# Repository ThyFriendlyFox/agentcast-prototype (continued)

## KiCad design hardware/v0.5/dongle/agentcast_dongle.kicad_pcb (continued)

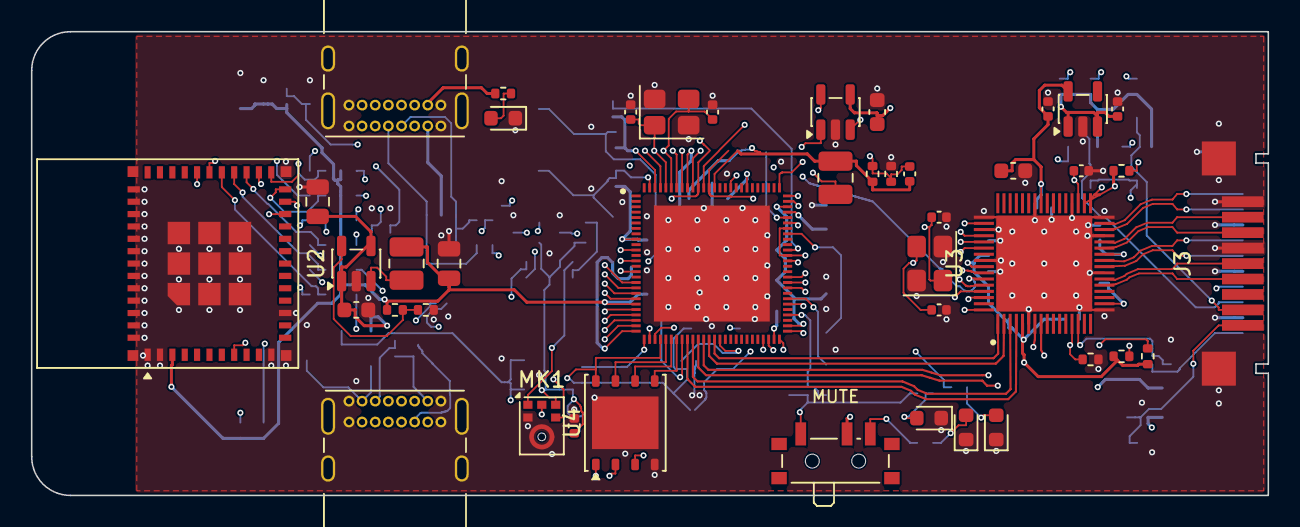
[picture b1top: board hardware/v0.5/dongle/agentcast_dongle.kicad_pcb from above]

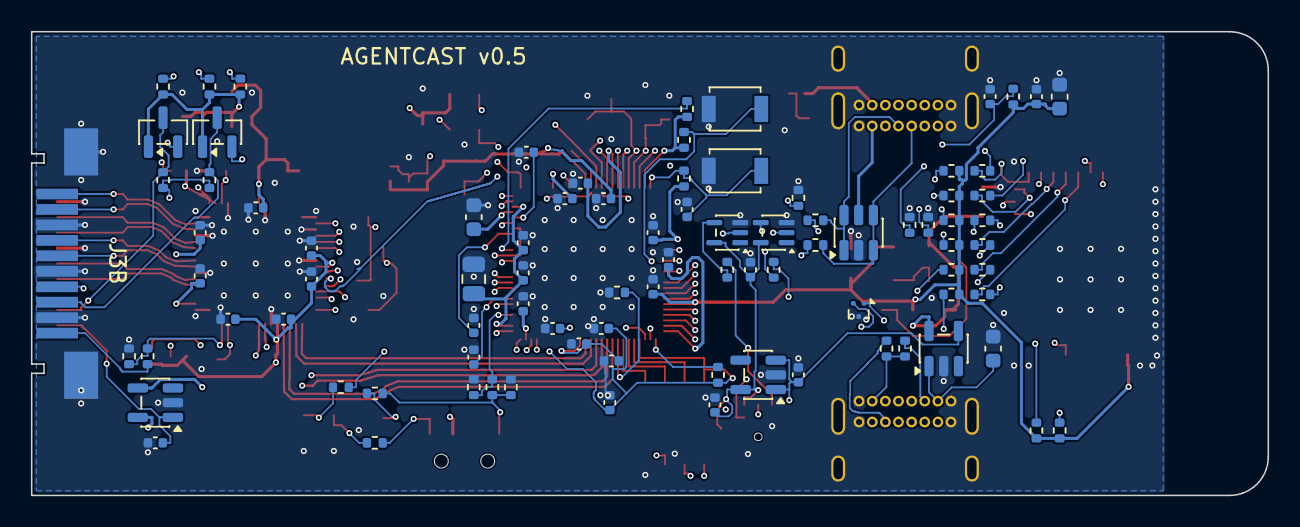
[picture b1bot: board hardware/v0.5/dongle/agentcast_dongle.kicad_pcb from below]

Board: 8 copper layers, 80.0 x 30.0 mm, 132 parts (89 on the bottom side), 100 nets.

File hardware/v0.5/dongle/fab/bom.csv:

"Refs","Value","Footprint","Qty","DNP"
"C1","100n","Capacitor_SMD:C_0402_1005Metric","1",""
"C2","100n","Capacitor_SMD:C_0402_1005Metric","1",""
"C3","100n","Capacitor_SMD:C_0402_1005Metric","1",""
"C4","100n","Capacitor_SMD:C_0402_1005Metric","1",""
"C5","100n","Capacitor_SMD:C_0402_1005Metric","1",""
"C6","100n","Capacitor_SMD:C_0402_1005Metric","1",""
"C7","100n","Capacitor_SMD:C_0402_1005Metric","1",""
"C8","100n","Capacitor_SMD:C_0402_1005Metric","1",""
"C9","100n","Capacitor_SMD:C_0402_1005Metric","1",""
"C10","100n","Capacitor_SMD:C_0402_1005Metric","1",""
"C11","100n","Capacitor_SMD:C_0402_1005Metric","1",""
"C12","100n","Capacitor_SMD:C_0402_1005Metric","1",""
"C13","10u","Capacitor_SMD:C_0603_1608Metric","1",""
"C14","22u","Capacitor_SMD:C_0805_2012Metric","1",""
"C15","1u","Capacitor_SMD:C_0402_1005Metric","1",""
"C16","1u","Capacitor_SMD:C_0402_1005Metric","1",""
"C17","1u","Capacitor_SMD:C_0402_1005Metric","1",""
"C18","1u","Capacitor_SMD:C_0402_1005Metric","1",""
"C19","4.7u","Capacitor_SMD:C_0603_1608Metric","1",""
"C20","22p","Capacitor_SMD:C_0402_1005Metric","1",""
"C21","12p","Capacitor_SMD:C_0402_1005Metric","1",""
"C22","12p","Capacitor_SMD:C_0402_1005Metric","1",""
"C23","1u","Capacitor_SMD:C_0402_1005Metric","1",""
"C24","100n","Capacitor_SMD:C_0402_1005Metric","1",""
"C25","100n","Capacitor_SMD:C_0402_1005Metric","1",""
"C26","100n","Capacitor_SMD:C_0402_1005Metric","1",""
"C27","100n","Capacitor_SMD:C_0402_1005Metric","1",""
"C28","100n","Capacitor_SMD:C_0402_1005Metric","1",""
"C29","100n","Capacitor_SMD:C_0402_1005Metric","1",""
"C30","100n","Capacitor_SMD:C_0402_1005Metric","1",""
"C31","100n","Capacitor_SMD:C_0402_1005Metric","1",""
"C32","10u","Capacitor_SMD:C_0603_1608Metric","1",""
"C33","2.2n","Capacitor_SMD:C_0402_1005Metric","1",""
"C34","12p","Capacitor_SMD:C_0402_1005Metric","1",""
"C35","12p","Capacitor_SMD:C_0402_1005Metric","1",""
"C36","1u","Capacitor_SMD:C_0402_1005Metric","1",""
"C37","1u","Capacitor_SMD:C_0402_1005Metric","1",""
"C38","100n","Capacitor_SMD:C_0402_1005Metric","1",""
"C39","10u","Capacitor_SMD:C_0603_1608Metric","1",""
"C40","100n","Capacitor_SMD:C_0402_1005Metric","1",""
"C41","1u","Capacitor_SMD:C_0402_1005Metric","1",""
"C42","10u","Capacitor_SMD:C_0603_1608Metric","1",""
"C43","22u","Capacitor_SMD:C_0805_2012Metric","1",""
"C44","22u","Capacitor_SMD:C_0805_2012Metric","1",""
"C45","10u","Capacitor_SMD:C_0603_1608Metric","1",""
"C46","1u","Capacitor_SMD:C_0402_1005Metric","1",""
"C47","1u","Capacitor_SMD:C_0402_1005Metric","1",""
"C48","100n","Capacitor_SMD:C_0402_1005Metric","1",""
"C49","100n","Capacitor_SMD:C_0402_1005Metric","1",""
"D1","green LIVE","LED_SMD:LED_0603_1608Metric","1",""
"D2","red MUTED","LED_SMD:LED_0603_1608Metric","1",""
"D3","green PWR","LED_SMD:LED_0603_1608Metric","1",""
"D4","amber STATE","LED_SMD:LED_0603_1608Metric","1",""
"J3","HDMI-003","Agentcast:HDMI_A_Plug_XUNPU_HDMI-003_Top","1",""
"J4","USB4085-GF-A","Connector_USB:USB_C_Receptacle_GCT_USB4085","1",""
"J6","USB4085-GF-A","Connector_USB:USB_C_Receptacle_GCT_USB4085","1",""
"L1","2.2u","Inductor_SMD:L_1008_2520Metric","1",""
"L2","2.2u","Inductor_SMD:L_1008_2520Metric","1",""
"MK1","ICS-43434","Sensor_Audio:InvenSense_ICS-43434-6_3.5x2.65mm","1",""
"Q1","BSS138","Package_TO_SOT_SMD:SOT-23","1",""
"Q2","BSS138","Package_TO_SOT_SMD:SOT-23","1",""
"R1","4.02k","Resistor_SMD:R_0402_1005Metric","1",""
"R2","499k","Resistor_SMD:R_0402_1005Metric","1",""
"R3","499k","Resistor_SMD:R_0402_1005Metric","1",""
"R4","10k","Resistor_SMD:R_0402_1005Metric","1",""
"R5","10k","Resistor_SMD:R_0402_1005Metric","1",""
"R6","10k","Resistor_SMD:R_0402_1005Metric","1",""
"R7","10k","Resistor_SMD:R_0402_1005Metric","1",""
"R8","6.04k","Resistor_SMD:R_0402_1005Metric","1",""
"R9","10k","Resistor_SMD:R_0402_1005Metric","1",""
"R10","4.7k","Resistor_SMD:R_0402_1005Metric","1",""
"R11","4.7k","Resistor_SMD:R_0402_1005Metric","1",""
"R12","18k","Resistor_SMD:R_0402_1005Metric","1",""
"R13","10k","Resistor_SMD:R_0402_1005Metric","1",""
"R14","1.8k","Resistor_SMD:R_0402_1005Metric","1",""
"R15","4.7k","Resistor_SMD:R_0402_1005Metric","1",""
"R16","1.8k","Resistor_SMD:R_0402_1005Metric","1",""
"R17","4.7k","Resistor_SMD:R_0402_1005Metric","1",""
"R18","27k","Resistor_SMD:R_0402_1005Metric","1",""
"R19","10k","Resistor_SMD:R_0402_1005Metric","1",""
"R20","10k","Resistor_SMD:R_0402_1005Metric","1",""
"R21","10k","Resistor_SMD:R_0402_1005Metric","1",""
"R22","22","Resistor_SMD:R_0402_1005Metric","1",""
"R23","10k","Resistor_SMD:R_0402_1005Metric","1",""
"R24","22","Resistor_SMD:R_0402_1005Metric","1",""
"R25","10k","Resistor_SMD:R_0402_1005Metric","1",""
"R26","22","Resistor_SMD:R_0402_1005Metric","1",""
"R27","10k","Resistor_SMD:R_0402_1005Metric","1",""
"R28","22","Resistor_SMD:R_0402_1005Metric","1",""
"R29","10k","Resistor_SMD:R_0402_1005Metric","1",""
"R30","22","Resistor_SMD:R_0402_1005Metric","1",""
"R31","10k","Resistor_SMD:R_0402_1005Metric","1",""
"R32","22","Resistor_SMD:R_0402_1005Metric","1",""
"R33","10k","Resistor_SMD:R_0402_1005Metric","1",""
"R34","5.1k","Resistor_SMD:R_0402_1005Metric","1",""
"R35","5.1k","Resistor_SMD:R_0402_1005Metric","1",""
"R36","22","Resistor_SMD:R_0402_1005Metric","1",""
"R37","22","Resistor_SMD:R_0402_1005Metric","1",""
"R38","100k","Resistor_SMD:R_0402_1005Metric","1",""
"R39","22.1k","Resistor_SMD:R_0402_1005Metric","1",""
"R40","56k","Resistor_SMD:R_0402_1005Metric","1",""
"R41","56k","Resistor_SMD:R_0402_1005Metric","1",""
"R42","100k","Resistor_SMD:R_0402_1005Metric","1",""
"R43","1k","Resistor_SMD:R_0402_1005Metric","1",""
"R44","1k","Resistor_SMD:R_0402_1005Metric","1",""
"R45","10k","Resistor_SMD:R_0402_1005Metric","1",""
"R46","100k","Resistor_SMD:R_0402_1005Metric","1",""
"R47","33","Resistor_SMD:R_0402_1005Metric","1",""
"R48","33","Resistor_SMD:R_0402_1005Metric","1",""
"R49","100k","Resistor_SMD:R_0402_1005Metric","1",""
"R50","2.2k","Resistor_SMD:R_0402_1005Metric","1",""
"R51","330","Resistor_SMD:R_0402_1005Metric","1",""
"SW1","BOOT","Button_Switch_SMD:SW_SPST_B3U-1000P","1",""
"SW2","PCM12SMTR","Button_Switch_SMD:SW_SPDT_PCM12","1",""
"SW3","RESET","Button_Switch_SMD:SW_SPST_B3U-1000P","1",""
"U1","ESP32-P4NRW32","Agentcast:QFN-104-1EP_10x10mm_P0.35mm_EP7.5x7.5mm","1",""
"U2","ESP32-C6-MINI-1","RF_Module:ESP32-C6-MINI-1","1",""
"U3","LT8912B","Agentcast:QFN-64-1EP_7.5x7.5mm_P0.4mm_EP6.2x6.2mm","1",""
"U4","W25Q128JVPIQ","Package_SON:WSON-8-1EP_6x5mm_P1.27mm_EP3.4x4.3mm","1",""
"U5","TLV62569DBV","Package_TO_SOT_SMD:SOT-23-5","1",""
"U6","TLV75518PDBV","Package_TO_SOT_SMD:SOT-23-5","1",""
"U7","TPS2051CDBV","Package_TO_SOT_SMD:SOT-23-5","1",""
"U8","USBLC6-2SC6","Package_TO_SOT_SMD:SOT-23-6","1",""
"U9","TLV62569DBV","Package_TO_SOT_SMD:SOT-23-5","1",""
"U10","TPD2EUSB30","Package_TO_SOT_SMD:Texas_DRT-3","1",""
"U11","TPS2051CDBV","Package_TO_SOT_SMD:SOT-23-5","1",""
"U12","AP2112K-1.8","Package_TO_SOT_SMD:SOT-23-5","1",""
"U13","74LVC1G34","Package_TO_SOT_SMD:SOT-353_SC-70-5","1",""
"U14","74LVC1G34","Package_TO_SOT_SMD:SOT-353_SC-70-5","1",""
"Y1","40MHz 10ppm","Crystal:Crystal_SMD_3225-4Pin_3.2x2.5mm","1",""
"Y2","25MHz (confirm)","Crystal:Crystal_SMD_3225-4Pin_3.2x2.5mm","1",""

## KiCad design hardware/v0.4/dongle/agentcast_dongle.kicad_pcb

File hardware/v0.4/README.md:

# Agentcast dongle v0.4

> **Archived** at commit `223e73b`. Superseded by [v0.5](../v0.5/) (own computer, 68 x 26 mm).
> Made from [v0.3](../v0.3/) (commit `f83c855`). v0.4 replaces the
> HDMI receptacle with a male HDMI Type-A plug: the stick goes straight into the TV.

One board, 67 x 46 mm, 4 layers. A Raspberry Pi Compute Module 5 sits on top.
A male HDMI plug clamps the near end of the board, like a Roku or Fire TV stick.

| | v0.3 | v0.4 |
|---|---|---|
| HDMI | Amphenol 10029449 receptacle; needed a male-to-male adapter | Male Type-A plug on the board edge (XUNPU HDMI-003 class); plugs into the TV |
| HDMI pairs | all four on F.Cu | D2 and D0 on F.Cu to the top contacts; D1 and CK drop through a via pair to the bottom contacts |
| Size, ports, mic, mute | as v0.3 | unchanged |

**Do not order yet.** The plug's footprint follows the HDMI Type-A contact
layout, but four of its numbers are the part's own and need its drawing (see
"HDMI plug").

| From above | From below | With the CM5 |
|---|---|---|
|  |  |  |
|  |  |  |

Schematic: [`dongle/docs/schematic.png`](dongle/docs/schematic.png).
Commands: `workcenter render dongle --views all --spin-frames 36 --strict`; the view
from below adds `--views spin --spin-frames 36 --spin-tilt -125`; the assembly
pictures come from `make assembly`.

## HDMI plug

A board-edge HDMI plug has its contacts in two rows that clamp the board: one
row solders to pads on the top face, the other to pads on the bottom face, both
at the board's edge. KiCad's library has no such footprint, so
[`library/gen_library.py`](library/gen_library.py) draws one as two footprints:
`HDMI_A_Plug_Edge_Top` (J3) and `HDMI_A_Plug_Edge_Bottom` (J3B, on B.Cu, not in
the BOM).

| Number | Value | Source |
|---|---|---|
| Contacts | 19, odd and even pins in two rows | HDMI Type-A pinout |
| Pitch in a row | 1.0 mm, the rows 0.5 mm apart | HDMI Type-A pinout |
| Shell | 13.9 x 4.45 mm, 11.5 mm beyond the edge (3D box) | HDMI Type-A plug size; length estimated |
| Pad size | 0.6 x 2.0 mm, ending 0.3 mm from the edge | **to confirm** on the part's drawing |
| Clamp tabs | 1.2 x 2.4 mm, 6.6 mm each side of the axis, both faces | **to confirm** |
| Odd row on the top face | yes (`ODD_ON_TOP`) | **to confirm** |
| Board thickness it clamps | 1.6 mm (this board) | **to confirm**; many stick plugs clamp 1.0 or 1.2 mm |

The candidate part is XUNPU HDMI-003 (LCSC
[C5723179](https://www.lcsc.com/product-detail/C5723179.html)), listed as a
19-pin male HDMI-A plug, "clamp plate" mount. Its drawing is a PDF I could not
open from this session. With the drawing, each **to confirm** line above is one
constant in `gen_library.py` (and `thickness=` on the design if the board must
be thinner); `make design` then regenerates the board.

If the odd row turns out to be on the bottom face, D2 and D0 move to the bottom
and D1 and CK to the top: `route_tmds()` reads the pads, so the pairs follow.

## Why it is not narrower

The CM5 is 55 x 40 mm, so a stick built on it is at least 40 mm wide. v0.4 is
46 mm: 40 for the module and a 6 mm strip below it that carries the four HDMI
pairs, the mic, two LEDs and the mute switch. A Roku Streaming Stick is about
20 mm wide; that size needs a smaller computer than the CM5.

## CM5 position, checked

Raspberry Pi's CM5 3D model (RP-007222-DD-2, "rpi-cm5 3D_STEP", from
[rpltd.co/cm5-design-files](https://rpltd.co/cm5-design-files)) gives, in the
module's frame (antenna edge at x = 0, y up):

| Feature | 3D model | This board |
|---|---|---|
| Board-to-board connectors (Amphenol 10164228-1001A1RLF) | centres (25.0, 3.0) and (25.0, 37.0) mm | J1, J2 at 25.0 mm from the antenna edge, 3.0 mm in from each long edge |
| M2.5 holes | (3.5, 3.5), (51.5, 3.5), (3.5, 36.5), (51.5, 36.5) mm, 2.7 mm | H1-H4 at the same points |
| U.FL | (2.567, 31.0) mm | matches datasheet Figure 4 (2.567 mm from the antenna edge, 9 mm from the top) |

The 3D model's connector names (P1, P2) do not follow the pin numbers, so which
socket carries pins 1-100 still comes from Figure 4's labels: the one nearer the
U.FL. The assembly pictures put Raspberry Pi's model on the board with these
numbers; its U.FL lands on the J1 side, as Figure 4 shows.

## Fabrication files

[`dongle/fab/`](dongle/fab/), made by `make fab`: Gerbers with the drill file
and job file (`gerbers/`), the BOM (`bom.csv`), the schematic PDF, and a
pick-and-place file for both faces (`agentcast_dongle-pos.csv`, KiCad CSV, mm,
page coordinates: the board's top-left corner is at (100, -100)). The BOM lists
values and footprints; part numbers for the passives are not chosen yet.

## Gate results

`workcenter gates dongle`:

| Gate | Result |
|---|---|
| ERC | PASS, 0 errors, 0 warnings |
| DRC | PASS, 0 errors, 0 unconnected, 0 parity; 4 silk warnings where the USB-C bodies and the mute switch cross the edge, as designed |
| SIM | PASS, 1 deck (`mic_live`) |
| EXPORT | PASS, 24 Gerber files, drill, BOM, PDF |

`workcenter render dongle --strict` passes: every part has a 3D body.

## Layout

| Where | What |
|---|---|
| Far end (x = 0) | The CM5's antenna. No copper and no parts under it, on any layer. |
| Under the module, F.Cu | J1, J2 and the HDMI pairs' risers. Nothing else: the module sits 1.5 mm above. |
| Strip below the module, F.Cu | Mic MK1 (sound hole at x 2.8, y 44.21 mm), LIVE and MUTED LEDs, mute switch SW2 (out of the long side), and the four HDMI pairs in lanes. |
| Near end | The male HDMI plug clamps the edge (J3 top contacts, J3B bottom contacts). USB-C power J4 out of the top side, USB-C external mic J6 out of the bottom side. |
| B.Cu | The plug's bottom contacts, and 32 small parts: power switches, ESD, clock buffers, PWR / ACT / STATE LEDs, resistors, capacitors, the BOOT button. |

## How it maps to the spec

| Spec requirement | v0.4 answer |
|---|---|
| HDMI dongle, the TV shows only what the dongle sends | CM5 HDMI0 to a male HDMI plug (J3, J3B) on the stick's end: it plugs into the TV. |
| A separate power supply | USB-C (J4). The CM5 negotiates 5 V up to 5 A itself (CM5 datasheet 2.12.1). |
| Hear the room; tell speakers apart | On-board ICS-43434 mic. Speakers are told apart by voice in the cloud, so one mic is enough. |
| A better mic when the room needs it | USB-C host port (J6) for a USB mic. |
| A physical mute; the indicator tied to mic power | SW2 cuts MIC_VDD. The green LIVE LED runs from MIC_VDD; the red MUTED LED from the switch's other throw. |
| Software cannot turn a mic on in secret | MIC_VDD powers the on-board mic, its clock buffers, and U3's enable, which powers J6. No GPIO can do either. |
| TV control over HDMI-CEC | HDMI pin 13 to the CM5's HDMI0_CEC. |
| Recovery without IT | BOOT button (nRPIBOOT) and USB data on J4 for `rpiboot`. |

## Part choices

| Ref | Part | Why |
|---|---|---|
| J1, J2 | Hirose DF40C-100DS-0.4V | The CM5 sockets. 1.5 mm stack height (CM5 datasheet 4.1.1). |
| J3, J3B | HDMI Type-A male plug, board-edge clamp (XUNPU HDMI-003 class) | Plugs straight into the TV. One part, two footprints (top and bottom contacts). See "HDMI plug". |
| J4, J6 | GCT USB4085 | USB-C 2.0, through-hole pins: strong against a plug pulled sideways, and KiCad has its 3D body. J4: power and flashing. J6: host port with 56 k Rp on each CC. |
| U1, U4 | ST USBLC6-2SC6 | ESD on each USB 2.0 pair. |
| U2 | TI TPS2051CDBV | HDMI +5V: current limit and reverse-current blocking. EN from +3V3. |
| U3 | TI TPS2051CDBV | External mic power. EN from MIC_VDD, so mute cuts it. |
| MK1 | TDK InvenSense ICS-43434 | I2S mic, 24-bit, bottom port. |
| U5, U6 | 74LVC1G34 | BCLK and WS buffers on MIC_VDD (Ioff): a muted mic gets no power through its clock pins. |
| SW2 | C&K PCM12SMTR | Mute slide switch, out of the long side. |
| SW1 | Omron B3U-1000P | BOOT button, bottom face. |

## Pin plan (CM5)

Read from the CM5 datasheet: the GPIO alternate-function table (section 2.9)
and the pinout (section 4.2). GPIO_VREF (pin 78) is tied to CM5_3.3V.

| Signal | CM5 pin | GPIO | Function | Goes to |
|---|---|---|---|---|
| I2S_BCLK | 49 | GPIO18 | I2S0_SCLK (alt a2), master | U5, R1, MK1 |
| I2S_WS | 26 | GPIO19 | I2S0_WS (alt a2) | U6, R2, MK1 |
| MIC_SD0 | 27 | GPIO20 | I2S0_SDI[0] (alt a2) | MK1 (left channel) |
| MIC_LIVE | 34 | GPIO5 | input, high = mic powered | R4 / R5 |
| STATE_LED | 30 | GPIO6 | output, high = LED on | R12, D3 |
| LED_nACT | 21 | - | activity LED sink, 20 mA max | D4 |
| nRPIBOOT | 93 | - | boot from USB when low | SW1 |
| CC1 / CC2 | 94 / 96 | - | USB-C PD | J4 |
| USB_P / USB_N | 105 / 103 | - | USB 2.0, device mode for rpiboot | J4 via U1 |
| USB3-0-DP / DM | 134 / 136 | - | USB 2.0 pair of USB 3.0 port 0, host | J6 via U4 |
| HDMI0 TX2/TX1/TX0/CLK | 170-190 (even) | - | TMDS | plug pins 1-12 (D2, D0 top; D1, CK bottom) |
| HDMI0_CEC / HOTPLUG | 151 / 153 | - | 5 V tolerant, direct | plug pins 13 / 19 (top) |
| HDMI0_SDA / SCL | 199 / 200 | - | 5 V tolerant, 1.8 k pull-ups in the CM5 | plug pins 16 (bottom) / 15 (top) |
| 5V | 77-87 (odd) | - | 4.75-5.25 V in | a bar between J1's rows, 3 vias to the In2.Cu plane |
| CM5_3.3V | 84, 86 | - | out, 600 mA total | GPIO_VREF, SW2, U2 EN |

## HDMI routing

The four TMDS pairs are drawn by hand in `route_tmds()`: 0.2 mm width, 0.2 mm
gap, 104 ohm differential on F.Cu over the In1.Cu ground plane
(JLC04161H-7628 stackup, Hammerstad-Jensen microstrip, edge-coupled). Each
pair leaves J2 downwards, runs in its own lane in the strip below the module,
rises beside the plug and turns in. D2 and D0 end on the plug's top pads. D1
and CK end on a via pair 2.0 mm from the edge (the vias 1.0 mm apart, the pad
pitch) and run the last 2.0 mm on B.Cu to the bottom pads. A ground via sits
beside each shield pin on both faces.

| Pair | Plug face | P | N | Skew |
|---|---|---|---|---|
| D2 | top | 66.761 mm | 66.761 mm | 0.000 mm |
| D1 | bottom | 68.861 mm | 68.861 mm | 0.000 mm |
| D0 | top | 70.961 mm | 70.961 mm | 0.000 mm |
| CK | bottom | 73.061 mm | 73.061 mm | 0.000 mm |

The CM5 asks for 0.15 mm within a pair and 25 mm between pairs (datasheet
2.5.1); the pairs here differ by 6.3 mm at most. The last 2.0 mm of D1 and CK
run on B.Cu over the In2.Cu +5V plane, not over ground.

Three nets are hand-routed where the router found no way: USB_H_DP and
HDMI_SCL each get a via just below their J2 pin (the HDMI lanes run under that
row), and HDMI_SCL runs on B.Cu across the board to a second via at plug pin 15.

## Simulation

`dongle/sim/mic_live.cir` checks the MIC_LIVE level at GPIO5 at its corners:

| Case | Limit | Result | Hand check |
|---|---|---|---|
| Live | >= 2.0 V (VIH) | 2.817 V | 3.135 x 99 / 109.1 - 3 uA x 9.165 k = 2.817 V |
| Muted | <= 0.8 V (VIL) | 0.303 V | 3 uA x 101 k = 0.303 V |

## Fab notes

- 4 layers, 1.6 mm, JLC04161H-7628 stackup or equal, with impedance control on
  the TMDS pairs (100 ohm differential, L1 to L2). F.Cu signal, In1.Cu GND
  plane, In2.Cu +5V plane, B.Cu signal.
- Smallest features: 0.15 mm track and gap, 0.45 mm via with a 0.25 mm hole.
- Parts on both faces; J4 and J6 are through-hole.

## Open items

1. **HDMI plug drawing.** Confirm pad size, clamp tabs, which face has the odd
   row, and the board thickness against the XUNPU HDMI-003 drawing (see "HDMI
   plug"). Its 3D body here is a box until the part's own model is in.
2. **Width.** 46 mm is set by the CM5. Narrower needs a smaller computer.
3. **Part numbers** for the passives in the BOM.
4. **Mic placement.** Behind a TV the mic hears less; the external USB mic is the fallback.
5. **USB-C current.** Check J4's VBUS rating against the CM5's measured load.
6. **Echo reference clock.** HDMI audio and I2S0 come from different blocks of the CM5.
7. **Mute switch direction.** Mark which slider end is LIVE on the first article.

## Commands

```bash
make verify     # lint, then workcenter gates
```

```bash
make fab        # gates, then Gerbers, drill, BOM, PDF and pick-and-place into dongle/fab/
```

```bash
make assembly   # fetch the CM5 model and render the board with the module on it
```

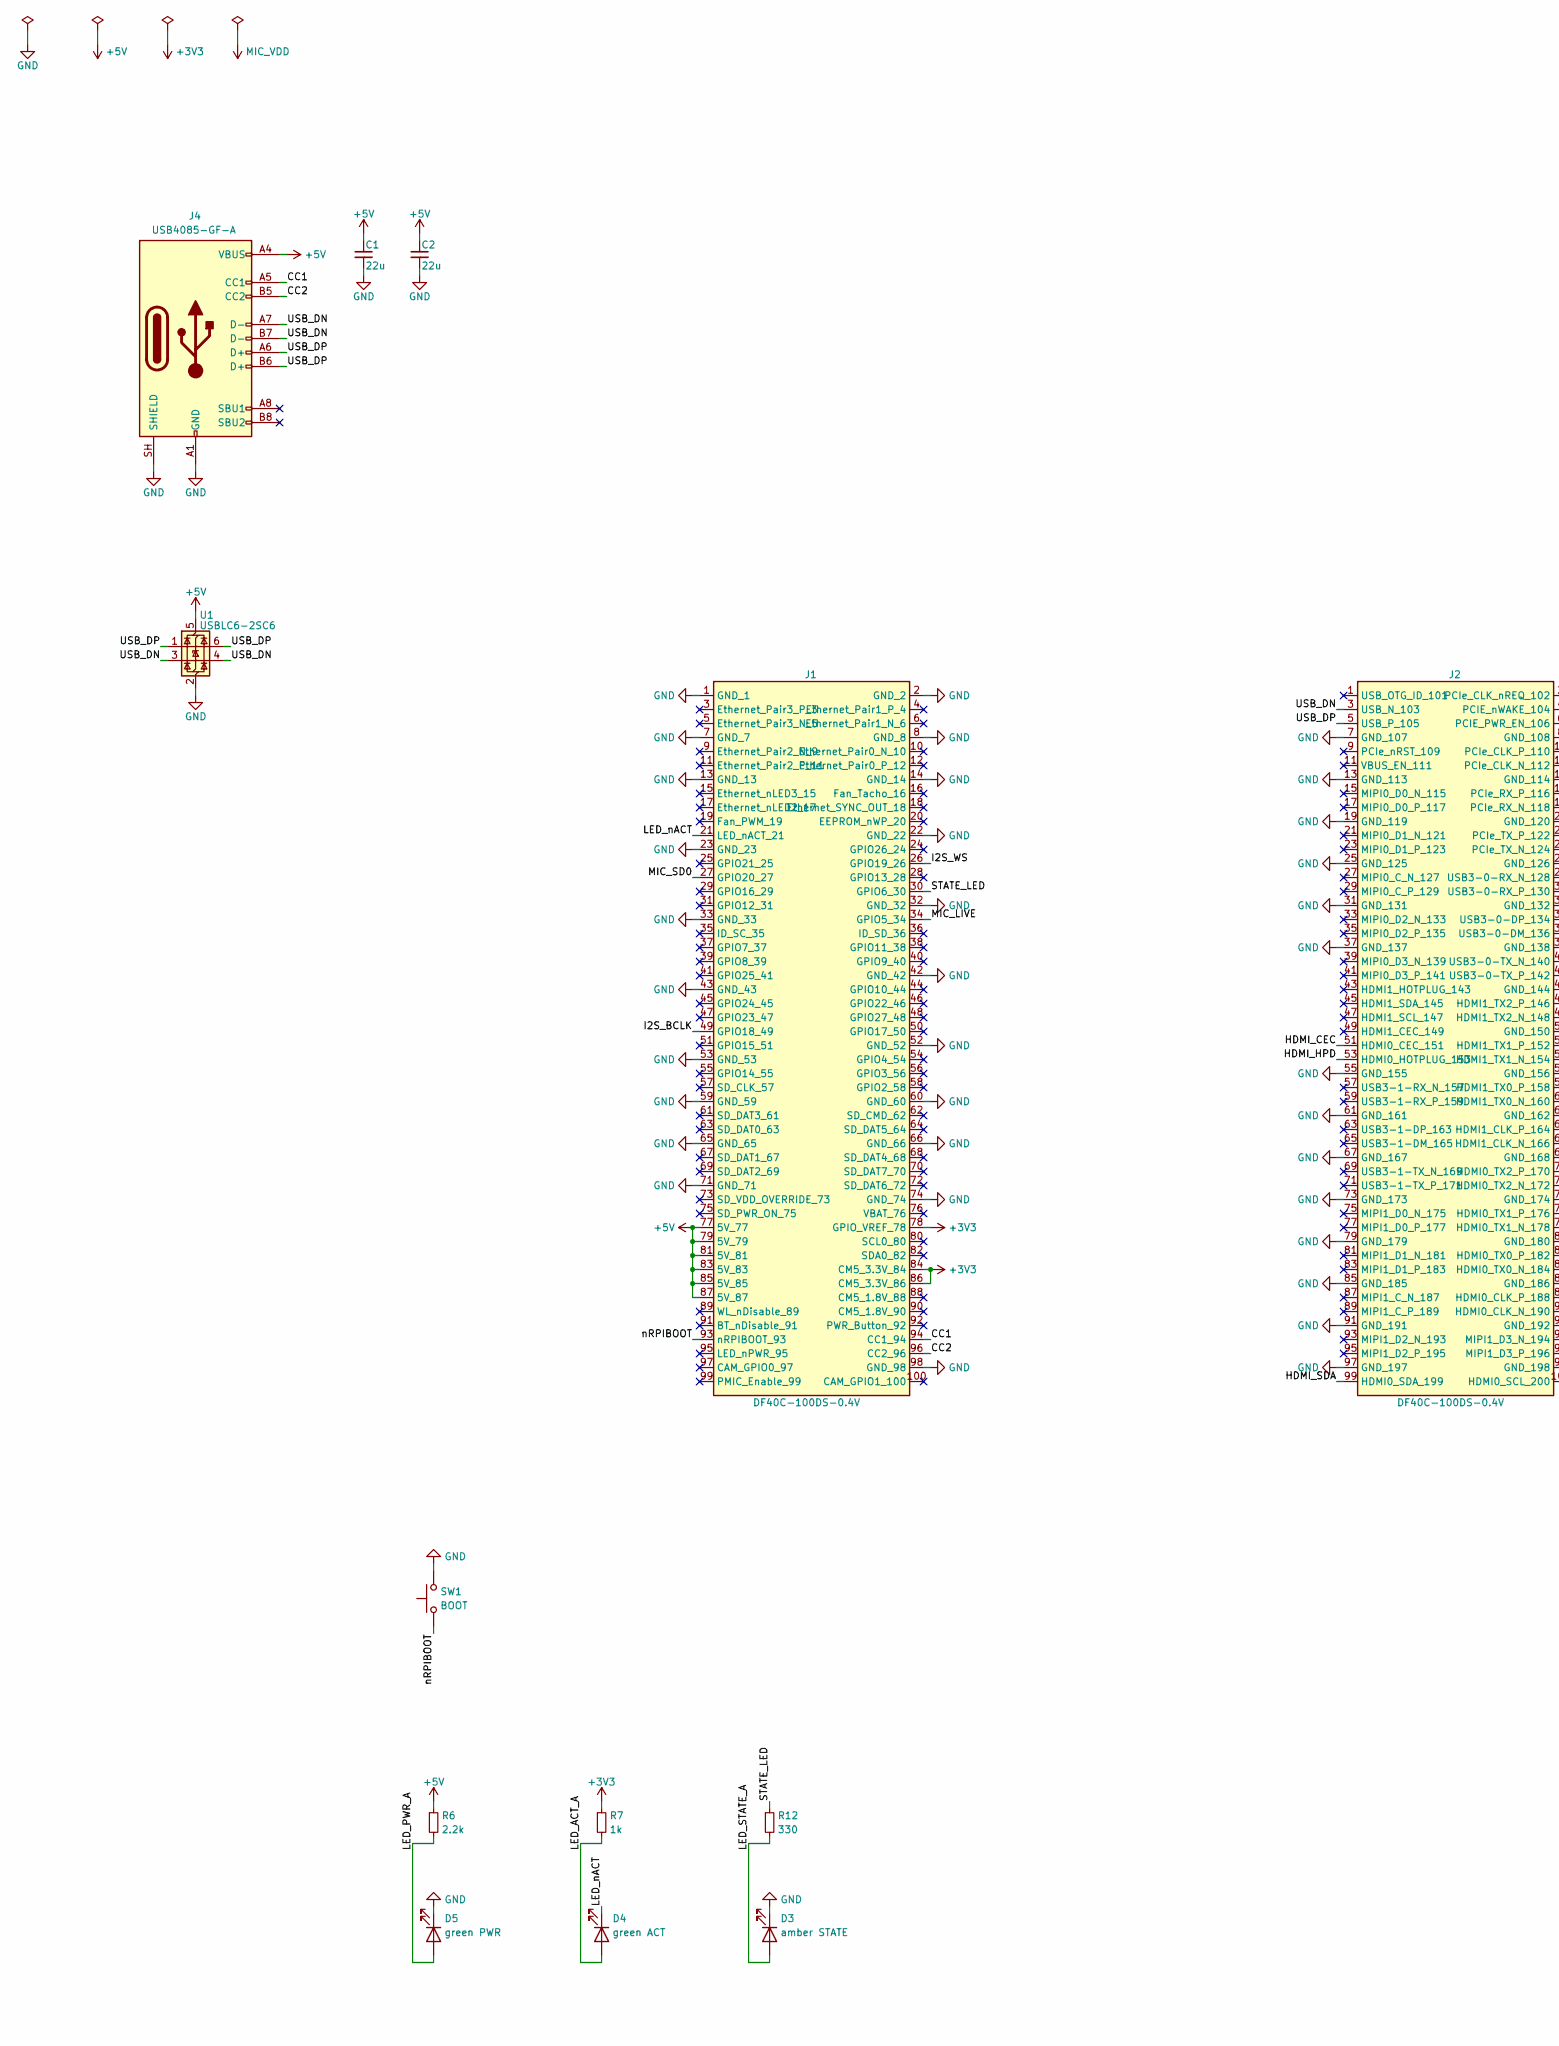
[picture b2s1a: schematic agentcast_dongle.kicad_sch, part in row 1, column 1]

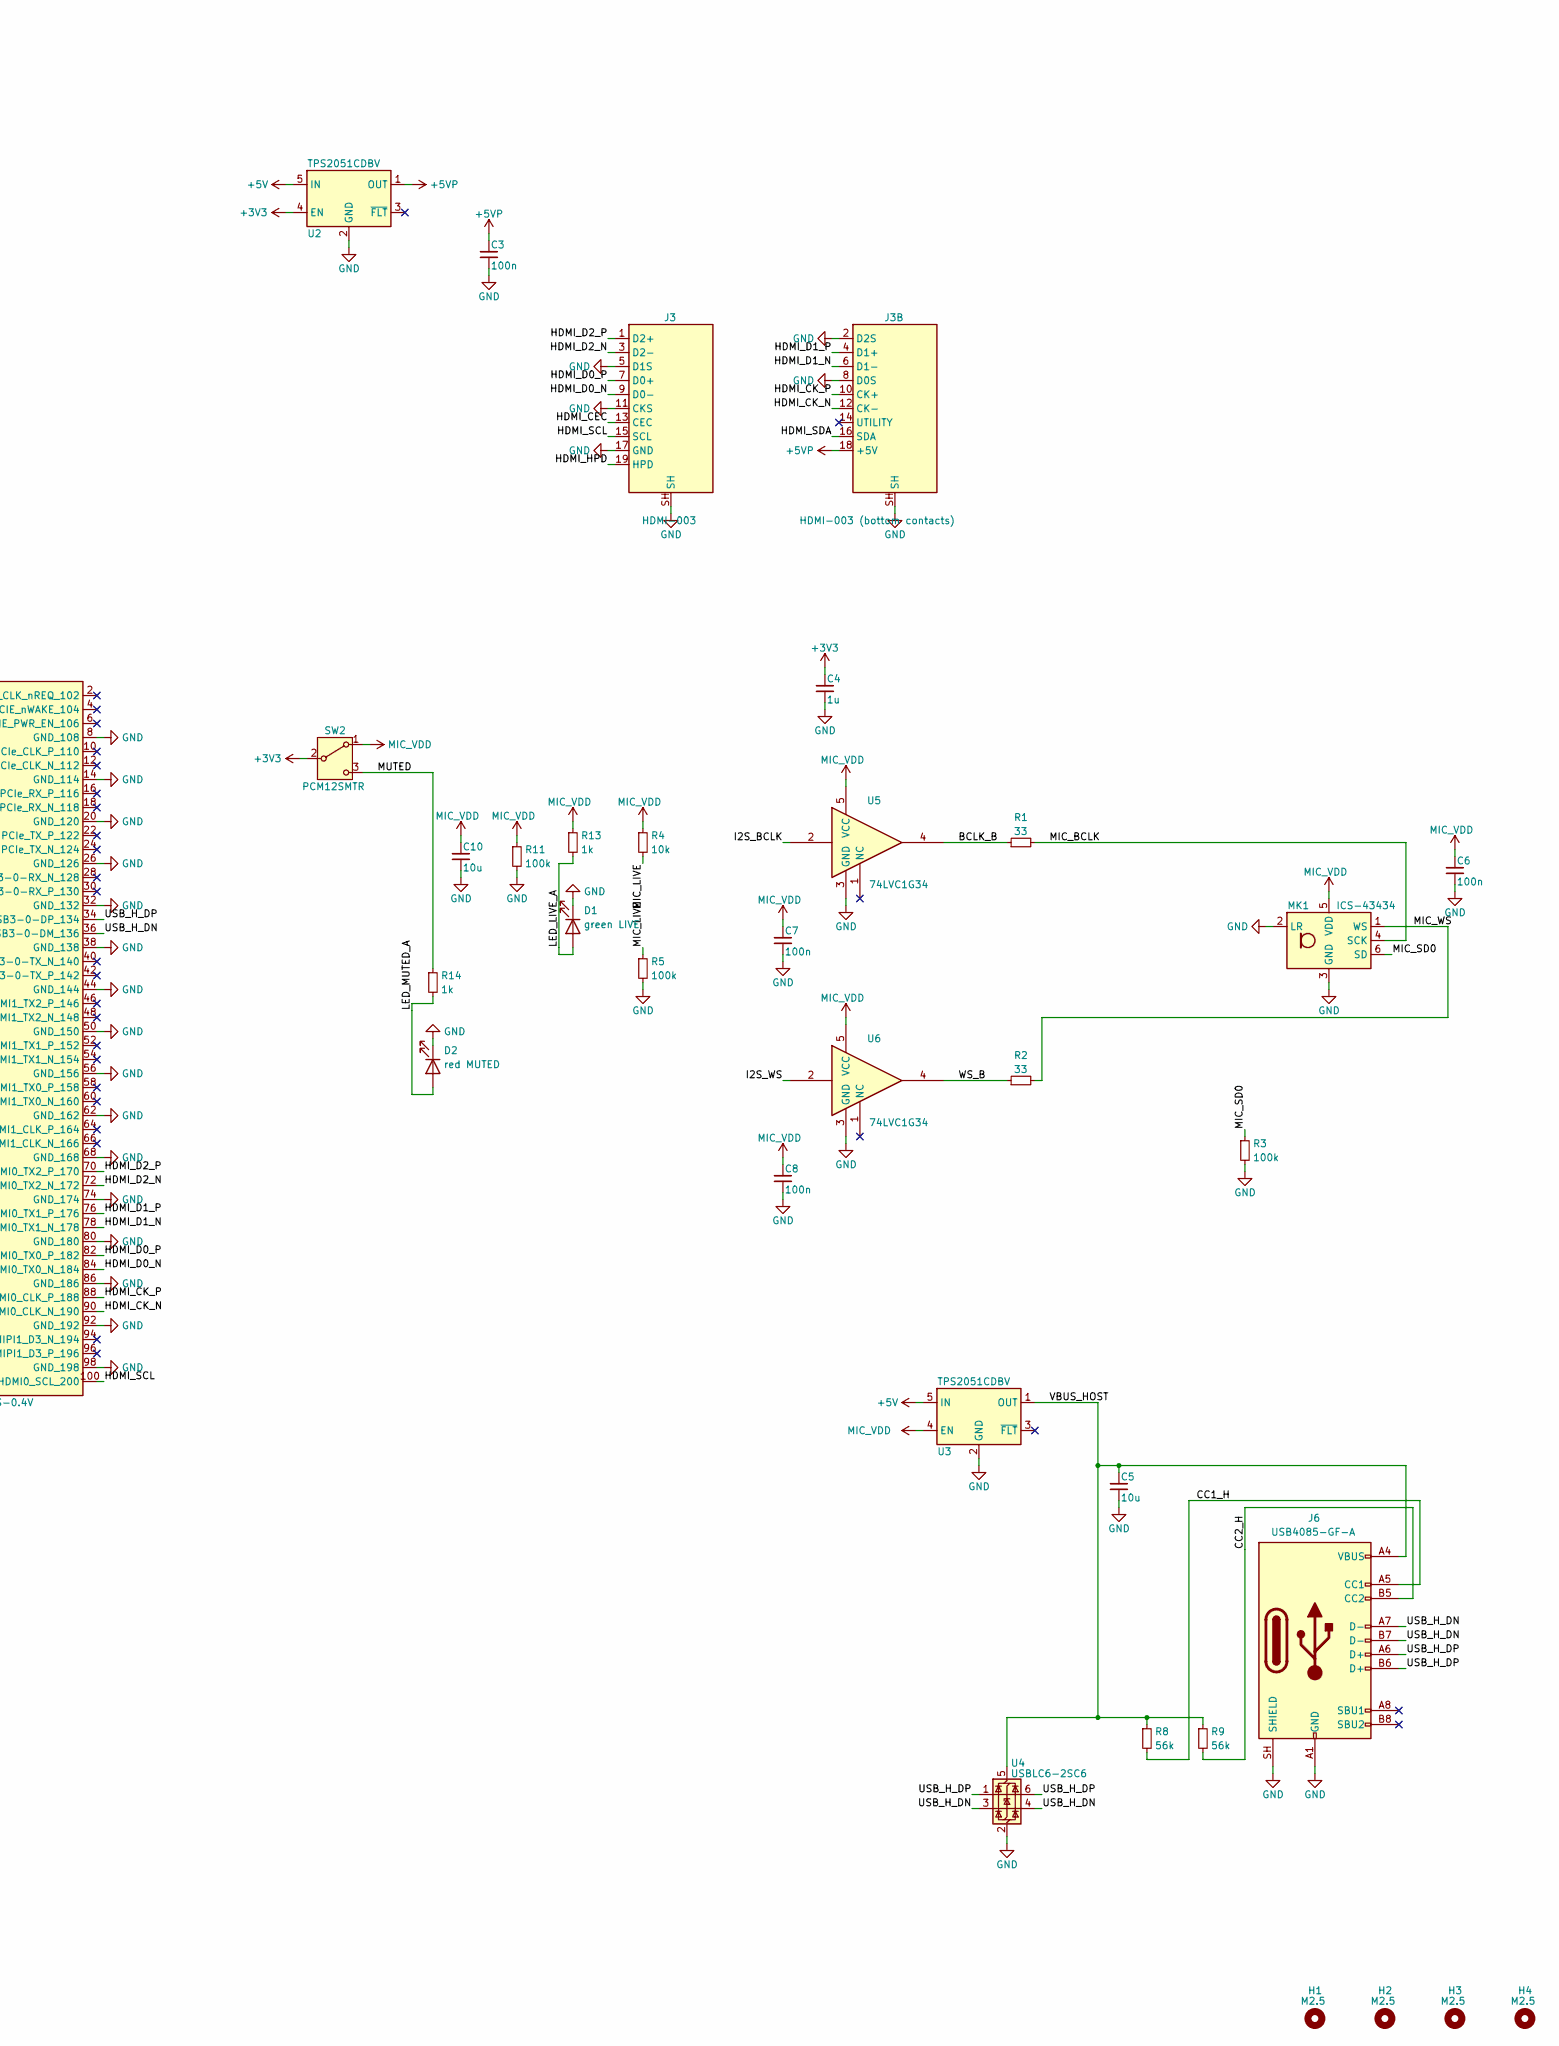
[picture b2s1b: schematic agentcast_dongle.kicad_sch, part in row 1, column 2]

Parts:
C1, C2: 22u; C_0805_2012Metric
C3, C6, C7, C8: 100n; C_0402_1005Metric
C4: 1u; C_0402_1005Metric
C5: 10u; C_0805_2012Metric
C10: 10u; C_0603_1608Metric
D1: green LIVE; LED_0603_1608Metric
D2: red MUTED; LED_0603_1608Metric
D3: amber STATE; LED_0603_1608Metric
D4: green ACT; LED_0603_1608Metric
D5: green PWR; LED_0603_1608Metric
H1, H2, H3, H4: M2.5; MountingHole_2.7mm_M2.5
J1, J2: DF40C-100DS-0.4V; Hirose_DF40C-100DS-0.4V_2x50_P0.4mm
J3: HDMI-003; HDMI_A_Plug_Edge_Top
J3B: HDMI-003 (bottom contacts); HDMI_A_Plug_Edge_Bottom
J4, J6: USB4085-GF-A; USB_C_Receptacle_GCT_USB4085
MK1: ICS-43434; InvenSense_ICS-43434-6_3.5x2.65mm
R1, R2: 33; R_0402_1005Metric
R3, R5, R11: 100k; R_0402_1005Metric
R4: 10k; R_0402_1005Metric
R6: 2.2k; R_0402_1005Metric
R7, R13, R14: 1k; R_0402_1005Metric
R8, R9: 56k; R_0402_1005Metric
R12: 330; R_0402_1005Metric
SW1: BOOT; SW_SPST_B3U-1000P
SW2: PCM12SMTR; SW_SPDT_PCM12
U1, U4: USBLC6-2SC6; SOT-23-6
U2, U3: TPS2051CDBV; SOT-23-5
U5, U6: 74LVC1G34; SOT-353_SC-70-5

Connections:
+3V3: C4.1, J1.78 (GPIO_VREF_78), J1.84 (CM5_3.3V_84), J1.86 (CM5_3.3V_86), R7.1, SW2.2 (B), U2.4 (EN)
+5V: C1.1, C2.1, J1.77 (5V_77), J1.79 (5V_79), J1.81 (5V_81), J1.83 (5V_83), J1.85 (5V_85), J1.87 (5V_87), J4.A4 (VBUS), J4.A9 (VBUS), J4.B4 (VBUS), J4.B9 (VBUS), R6.1, U1.5 (VBUS), U2.5 (IN), U3.5 (IN)
+5VP: C3.1, J3B.18 (+5V), U2.1 (OUT)
/BCLK_B: R1.1, U5.4
/CC1: J1.94 (CC1_94), J4.A5 (CC1)
/CC1_H: J6.A5 (CC1), R8.2
/CC2: J1.96 (CC2_96), J4.B5 (CC2)
/CC2_H: J6.B5 (CC2), R9.2
/HDMI_CEC: J2.51 (HDMI0_CEC_151), J3.13 (CEC)
/HDMI_CK_N: J2.90 (HDMI0_CLK_N_190), J3B.12 (CK-)
/HDMI_CK_P: J2.88 (HDMI0_CLK_P_188), J3B.10 (CK+)
/HDMI_D0_N: J2.84 (HDMI0_TX0_N_184), J3.9 (D0-)
/HDMI_D0_P: J2.82 (HDMI0_TX0_P_182), J3.7 (D0+)
/HDMI_D1_N: J2.78 (HDMI0_TX1_N_178), J3B.6 (D1-)
/HDMI_D1_P: J2.76 (HDMI0_TX1_P_176), J3B.4 (D1+)
/HDMI_D2_N: J2.72 (HDMI0_TX2_N_172), J3.3 (D2-)
/HDMI_D2_P: J2.70 (HDMI0_TX2_P_170), J3.1 (D2+)
/HDMI_HPD: J2.53 (HDMI0_HOTPLUG_153), J3.19 (HPD)
/HDMI_SCL: J2.100 (HDMI0_SCL_200), J3.15 (SCL)
/HDMI_SDA: J2.99 (HDMI0_SDA_199), J3B.16 (SDA)
/I2S_BCLK: J1.49 (GPIO18_49), U5.2
/I2S_WS: J1.26 (GPIO19_26), U6.2
/LED_ACT_A: D4.2 (A), R7.2
/LED_LIVE_A: D1.2 (A), R13.2
/LED_MUTED_A: D2.2 (A), R14.2
/LED_PWR_A: D5.2 (A), R6.2
/LED_STATE_A: D3.2 (A), R12.2
/LED_nACT: D4.1 (K), J1.21 (LED_nACT_21)
/MIC_BCLK: MK1.4 (SCK), R1.2
/MIC_LIVE: J1.34 (GPIO5_34), R4.2, R5.1
/MIC_SD0: J1.27 (GPIO20_27), MK1.6 (SD), R3.1
/MIC_WS: MK1.1 (WS), R2.2
/MUTED: R14.1, SW2.3 (C)
/STATE_LED: J1.30 (GPIO6_30), R12.1
/USB_DN: J2.3 (USB_N_103), J4.A7 (D-), J4.B7 (D-), U1.3 (I/O2), U1.4 (I/O2)
/USB_DP: J2.5 (USB_P_105), J4.A6 (D+), J4.B6 (D+), U1.1 (I/O1), U1.6 (I/O1)
/USB_H_DN: J2.36 (USB3-0-DM_136), J6.A7 (D-), J6.B7 (D-), U4.3 (I/O2), U4.4 (I/O2)
/USB_H_DP: J2.34 (USB3-0-DP_134), J6.A6 (D+), J6.B6 (D+), U4.1 (I/O1), U4.6 (I/O1)
/VBUS_HOST: C5.1, J6.A4 (VBUS), J6.A9 (VBUS), J6.B4 (VBUS), J6.B9 (VBUS), R8.1, R9.1, U3.1 (OUT), U4.5 (VBUS)
/WS_B: R2.1, U6.4
/nRPIBOOT: J1.93 (nRPIBOOT_93), SW1.1
GND: C1.2, C2.2, C3.2, C4.2, C5.2, C6.2, C7.2, C8.2, C10.2, D1.1 (K), D2.1 (K), D3.1 (K), D5.1 (K), J1.1 (GND_1), J1.2 (GND_2), J1.7 (GND_7), J1.8 (GND_8), J1.13 (GND_13), J1.14 (GND_14), J1.22 (GND_22), J1.23 (GND_23), J1.32 (GND_32), J1.33 (GND_33), J1.42 (GND_42), J1.43 (GND_43), J1.52 (GND_52), J1.53 (GND_53), J1.59 (GND_59), J1.60 (GND_60), J1.65 (GND_65), J1.66 (GND_66), J1.71 (GND_71), J1.74 (GND_74), J1.98 (GND_98), J2.7 (GND_107), J2.8 (GND_108), J2.13 (GND_113), J2.14 (GND_114), J2.19 (GND_119), J2.20 (GND_120), J2.25 (GND_125), J2.26 (GND_126), J2.31 (GND_131), J2.32 (GND_132), J2.37 (GND_137), J2.38 (GND_138), J2.44 (GND_144), J2.50 (GND_150), J2.55 (GND_155), J2.56 (GND_156), J2.61 (GND_161), J2.62 (GND_162), J2.67 (GND_167), J2.68 (GND_168), J2.73 (GND_173), J2.74 (GND_174), J2.79 (GND_179), J2.80 (GND_180), J2.85 (GND_185), J2.86 (GND_186), J2.91 (GND_191), J2.92 (GND_192), J2.97 (GND_197), J2.98 (GND_198), J3.5 (D1S), J3.11 (CKS), J3.17 (GND), J3.SH, J3B.2 (D2S), J3B.8 (D0S), J3B.SH, J4.A1 (GND), J4.A12 (GND), J4.B1 (GND), J4.B12 (GND), J4.SH (SHIELD), J6.A1 (GND), J6.A12 (GND), J6.B1 (GND), J6.B12 (GND), J6.SH (SHIELD), MK1.2 (LR), MK1.3 (GND), R3.2, R5.2, R11.2, SW1.2, U1.2 (GND), U2.2 (GND), U3.2 (GND), U4.2 (GND), U5.3 (GND), U6.3 (GND)
MIC_VDD: C6.1, C7.1, C8.1, C10.1, MK1.5 (VDD), R4.1, R11.1, R13.1, SW2.1 (A), U3.4 (EN), U5.5 (VCC), U6.5 (VCC)

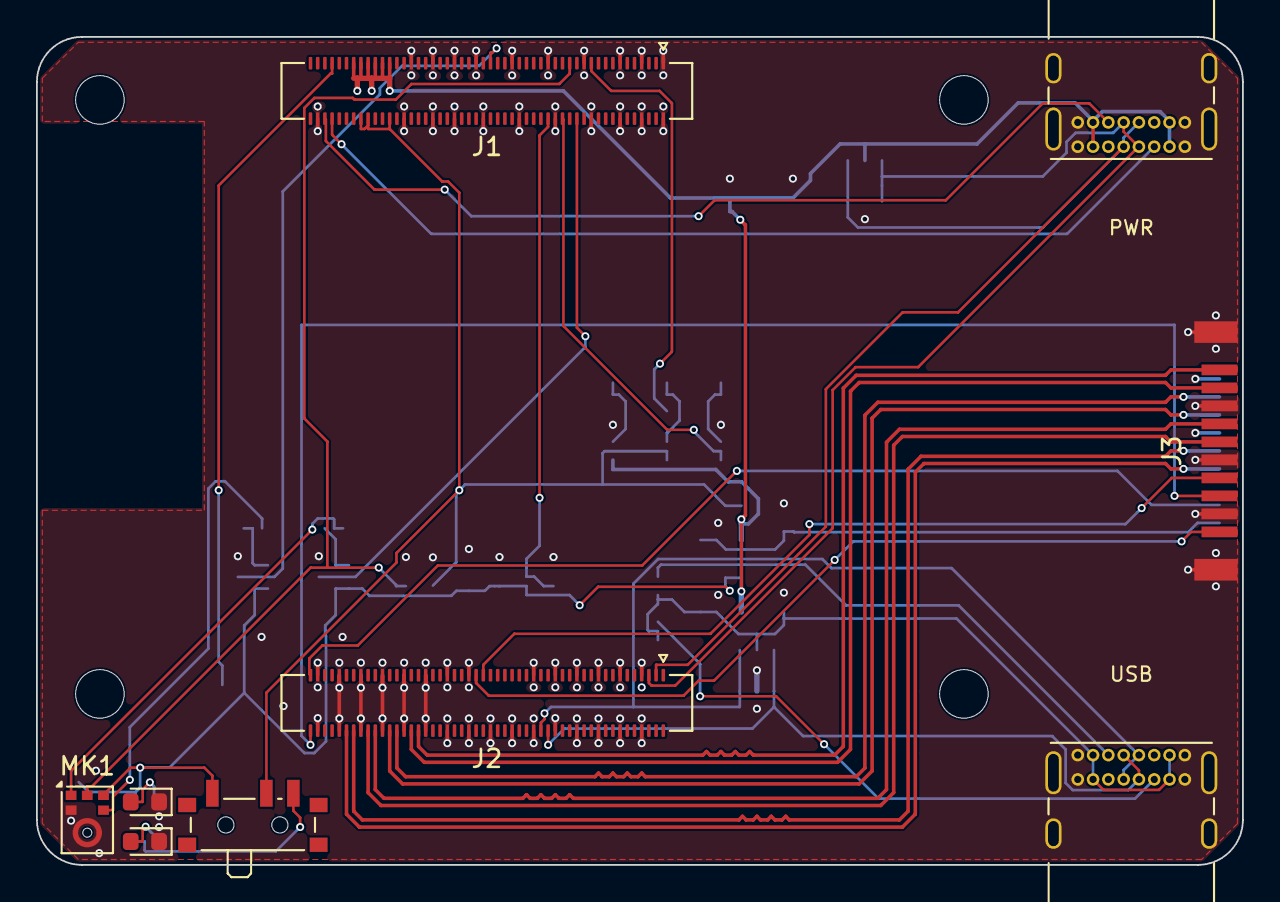
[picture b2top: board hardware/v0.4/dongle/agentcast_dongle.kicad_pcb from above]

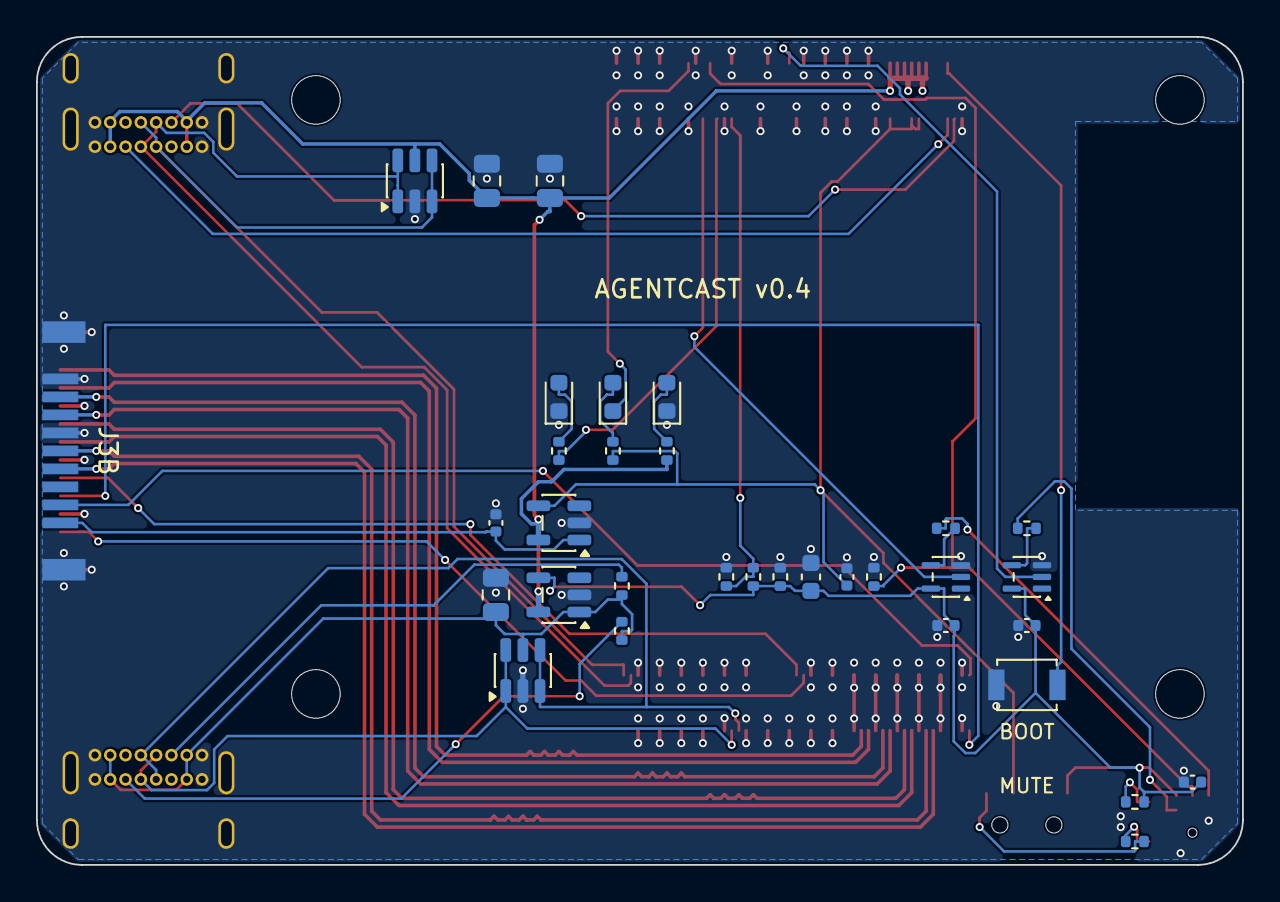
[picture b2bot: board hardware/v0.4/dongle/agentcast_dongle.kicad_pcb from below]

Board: 4 copper layers, 67.0 x 46.0 mm, 46 parts (33 on the bottom side), 43 nets.

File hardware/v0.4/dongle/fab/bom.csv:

"Refs","Value","Footprint","Qty","DNP"
"C1","22u","Capacitor_SMD:C_0805_2012Metric","1",""
"C2","22u","Capacitor_SMD:C_0805_2012Metric","1",""
"C3","100n","Capacitor_SMD:C_0402_1005Metric","1",""
"C4","1u","Capacitor_SMD:C_0402_1005Metric","1",""
"C5","10u","Capacitor_SMD:C_0805_2012Metric","1",""
"C6","100n","Capacitor_SMD:C_0402_1005Metric","1",""
"C7","100n","Capacitor_SMD:C_0402_1005Metric","1",""
"C8","100n","Capacitor_SMD:C_0402_1005Metric","1",""
"C10","10u","Capacitor_SMD:C_0603_1608Metric","1",""
"D1","green LIVE","LED_SMD:LED_0603_1608Metric","1",""
"D2","red MUTED","LED_SMD:LED_0603_1608Metric","1",""
"D3","amber STATE","LED_SMD:LED_0603_1608Metric","1",""
"D4","green ACT","LED_SMD:LED_0603_1608Metric","1",""
"D5","green PWR","LED_SMD:LED_0603_1608Metric","1",""
"J1","DF40C-100DS-0.4V","Connector_Hirose_DF40:Hirose_DF40C-100DS-0.4V_2x50_P0.4mm","1",""
"J2","DF40C-100DS-0.4V","Connector_Hirose_DF40:Hirose_DF40C-100DS-0.4V_2x50_P0.4mm","1",""
"J3","HDMI-003","Agentcast:HDMI_A_Plug_Edge_Top","1",""
"J4","USB4085-GF-A","Connector_USB:USB_C_Receptacle_GCT_USB4085","1",""
"J6","USB4085-GF-A","Connector_USB:USB_C_Receptacle_GCT_USB4085","1",""
"MK1","ICS-43434","Sensor_Audio:InvenSense_ICS-43434-6_3.5x2.65mm","1",""
"R1","33","Resistor_SMD:R_0402_1005Metric","1",""
"R2","33","Resistor_SMD:R_0402_1005Metric","1",""
"R3","100k","Resistor_SMD:R_0402_1005Metric","1",""
"R4","10k","Resistor_SMD:R_0402_1005Metric","1",""
"R5","100k","Resistor_SMD:R_0402_1005Metric","1",""
"R6","2.2k","Resistor_SMD:R_0402_1005Metric","1",""
"R7","1k","Resistor_SMD:R_0402_1005Metric","1",""
"R8","56k","Resistor_SMD:R_0402_1005Metric","1",""
"R9","56k","Resistor_SMD:R_0402_1005Metric","1",""
"R11","100k","Resistor_SMD:R_0402_1005Metric","1",""
"R12","330","Resistor_SMD:R_0402_1005Metric","1",""
"R13","1k","Resistor_SMD:R_0402_1005Metric","1",""
"R14","1k","Resistor_SMD:R_0402_1005Metric","1",""
"SW1","BOOT","Button_Switch_SMD:SW_SPST_B3U-1000P","1",""
"SW2","PCM12SMTR","Button_Switch_SMD:SW_SPDT_PCM12","1",""
"U1","USBLC6-2SC6","Package_TO_SOT_SMD:SOT-23-6","1",""
"U2","TPS2051CDBV","Package_TO_SOT_SMD:SOT-23-5","1",""
"U3","TPS2051CDBV","Package_TO_SOT_SMD:SOT-23-5","1",""
"U4","USBLC6-2SC6","Package_TO_SOT_SMD:SOT-23-6","1",""
"U5","74LVC1G34","Package_TO_SOT_SMD:SOT-353_SC-70-5","1",""
"U6","74LVC1G34","Package_TO_SOT_SMD:SOT-353_SC-70-5","1",""
